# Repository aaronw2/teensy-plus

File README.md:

Teensy Plus
Revision 3.3

Copyright (C) 2019 by Aaron Williams

This board is designed to be mounted to a PJRC Teensy 4.0 and 3.2 board.
It brings out the I/Os of the Teensy and provides a 3V to 5V level shifter
and a WS2813mini NeoPixel in order to drive up to four channels of
NeoPixels.  The 5V channels should be compatible with the FastLED library
for the Teensy 4.0 (not 3.2).  In addition, this board provides a switchable
12V, 500ma output for driving a fan or other 12V accessories.  Note that
while the boost circuit is fairly efficient that it will draw around 2.75 times
as much current at 5V as the 12V output, so at 500ma it could potentially
draw around 1.4 amps.  If the 12V is not needed then it does not need to be
stuffed.

This board is designed to be mounted back-to-back with the Teensy 3.2 or
4.0 board. Note that the extra pins on the back will not be accessible
once this board is soldered in place.  It can be connected by soldering
board headers or using headers and sockets.

Not all of the pins are used and not all need to be hooked up.

On/OFF, Program and VBat are not hooked up.  Additionally J9 does not
need to be connected and can be used for an additional 5V pin.

IO0, IO1, IO2 and IO3 are passed to the level shifter and IO23 is
connected to the enable pin of the level shifter.  IO3 then goes to
the WS2813mini.

3.3V is obtained from the Teensy board which cannot supply a lot of
current.  Please do not exceed 100ma.

J8 brings provides 3.3V, ground and IO4 through IO15.  The pinout is:
J8:
1.  3.3V
2.  GND
3.  IO0
4.  IO1
5.  IO2
6.  IO3
7.  IO5
8.  IO4
9.  IO10
10. IO11
11. IO12
12. IO13
13. IO14
14. IO15

These pins are directly connected.

J10 brings out the other pins along with the 5V level shifted pins.  Note
that the level shifted pins pass through 22 ohm resistors to help reduce
noise and can optionally have capacitors connected in order to create a
low-pass filter.

Pins 2-5 pass through the level shifter, however, pin1 is an output only
that is connected to the output of the WS2813mini.

J10:
1.  GND
2.  IO8  (5V)
3.  IO9  (5V)
4.  IO6  (5V)
5.  DO   (5V, output of WS2813-mini)
6.  IO17 (3.3v, bi-directional)
7.  IO18 (3.3v, bi-directional)
8.  IO19 (3.3v, bi-directional)
9.  IO20 (3.3v, bi-directional)
10. IO21 (3.3v, bi-directional)
11. IO22 (3.3v, bi-directional)
12. 3.3V (output)
13. 5V (output)
14. Ground

J11 is used for power input and output.
1. Ground
2. +5V
3. Ground
4. +5V
5. Ground
6. +5V
7. Ground
8. +3.3V

J12 is also used for power.
1. +5V
2. Ground

J201 provides 12V at up to 500ma.
1. GND
2. +12
3. Switched ground (IO17 high enables ground), used for turning fans on/off

Power: This board can either provide 5V or receive 5V from the Teensy.
Note that it expects a battery to not be hooked up and for the input
to already be regulated to 5V.

3.3V comes from the Teensy.  Note that the Teensy can only supply a limited
amount of current at 3.3V.

Level shifter:
A SN74AHCT125N buffer is used to provide 5V I/O.  IO23 is connected
directly to the enable pin and must be pulled low in order to enable the
5V I/O. Pulling IO23 high will tri-state the bi-directional level shifter.

NOTE: Only use the Texas Instraments SN74AHCT125N!  Other manufacturers
do not support 3V input.

BOM:
C1, C2, C4, C8, C13     CAP CER 0.1UF 16V X7R 0603
C3, C65, C12            CAP CER 1UF 25V X7R 0603
C9, C10, C11, C14       CAP CER 10UF 10V X7R 0805
D1                      WS2813-MINI neopixel, available from LCSC
RN1                     47K Panasonic EXB-Q16P473J Resistor Netowrk 15
U1                      SN74AHCT125N (TI only!!!)

12V BOM:
C201                    CAP CER 22UF 16V X5R 0603
C202                    CAP CER 0.1UF 16V X7R 0603
C203                    CAP CER 0.022UF 50V X7R 0603
C204                    CAP CER 820PF 50V X7R 0603
C205                    CAP CER 0.047UF 50V X7R 0603
C206                    CAP CER 47UF 16V X5R 1210
D201                    SS24FL DIODE SCHOTTKY 40V 2A SOD123F
Q201                    BSS214NW MOSFET N-CH 20V 1.5A SOT323
R201                    RES SMD 18.7K OHM 1% 1/10W 0603
R202                    RES SMD 1.62K OHM 1% 1/10W 0603
R203                    RES SMD 86.6K OHM 1% 1/10W 0603
R204                    RES SMD 10K OHM 1% 1/10W 0603
R205                    RES SMD 100K OHM 1% 1/10W 0603
                        (can use 86.6K or higher resistor)

All components except the WS2813-mini can be sourced from Digikey.
Why did I use a WS2813-mini? I bought a reel of 1500 of them and the
footprint I have is a bit smaller than the WS2812-mini.

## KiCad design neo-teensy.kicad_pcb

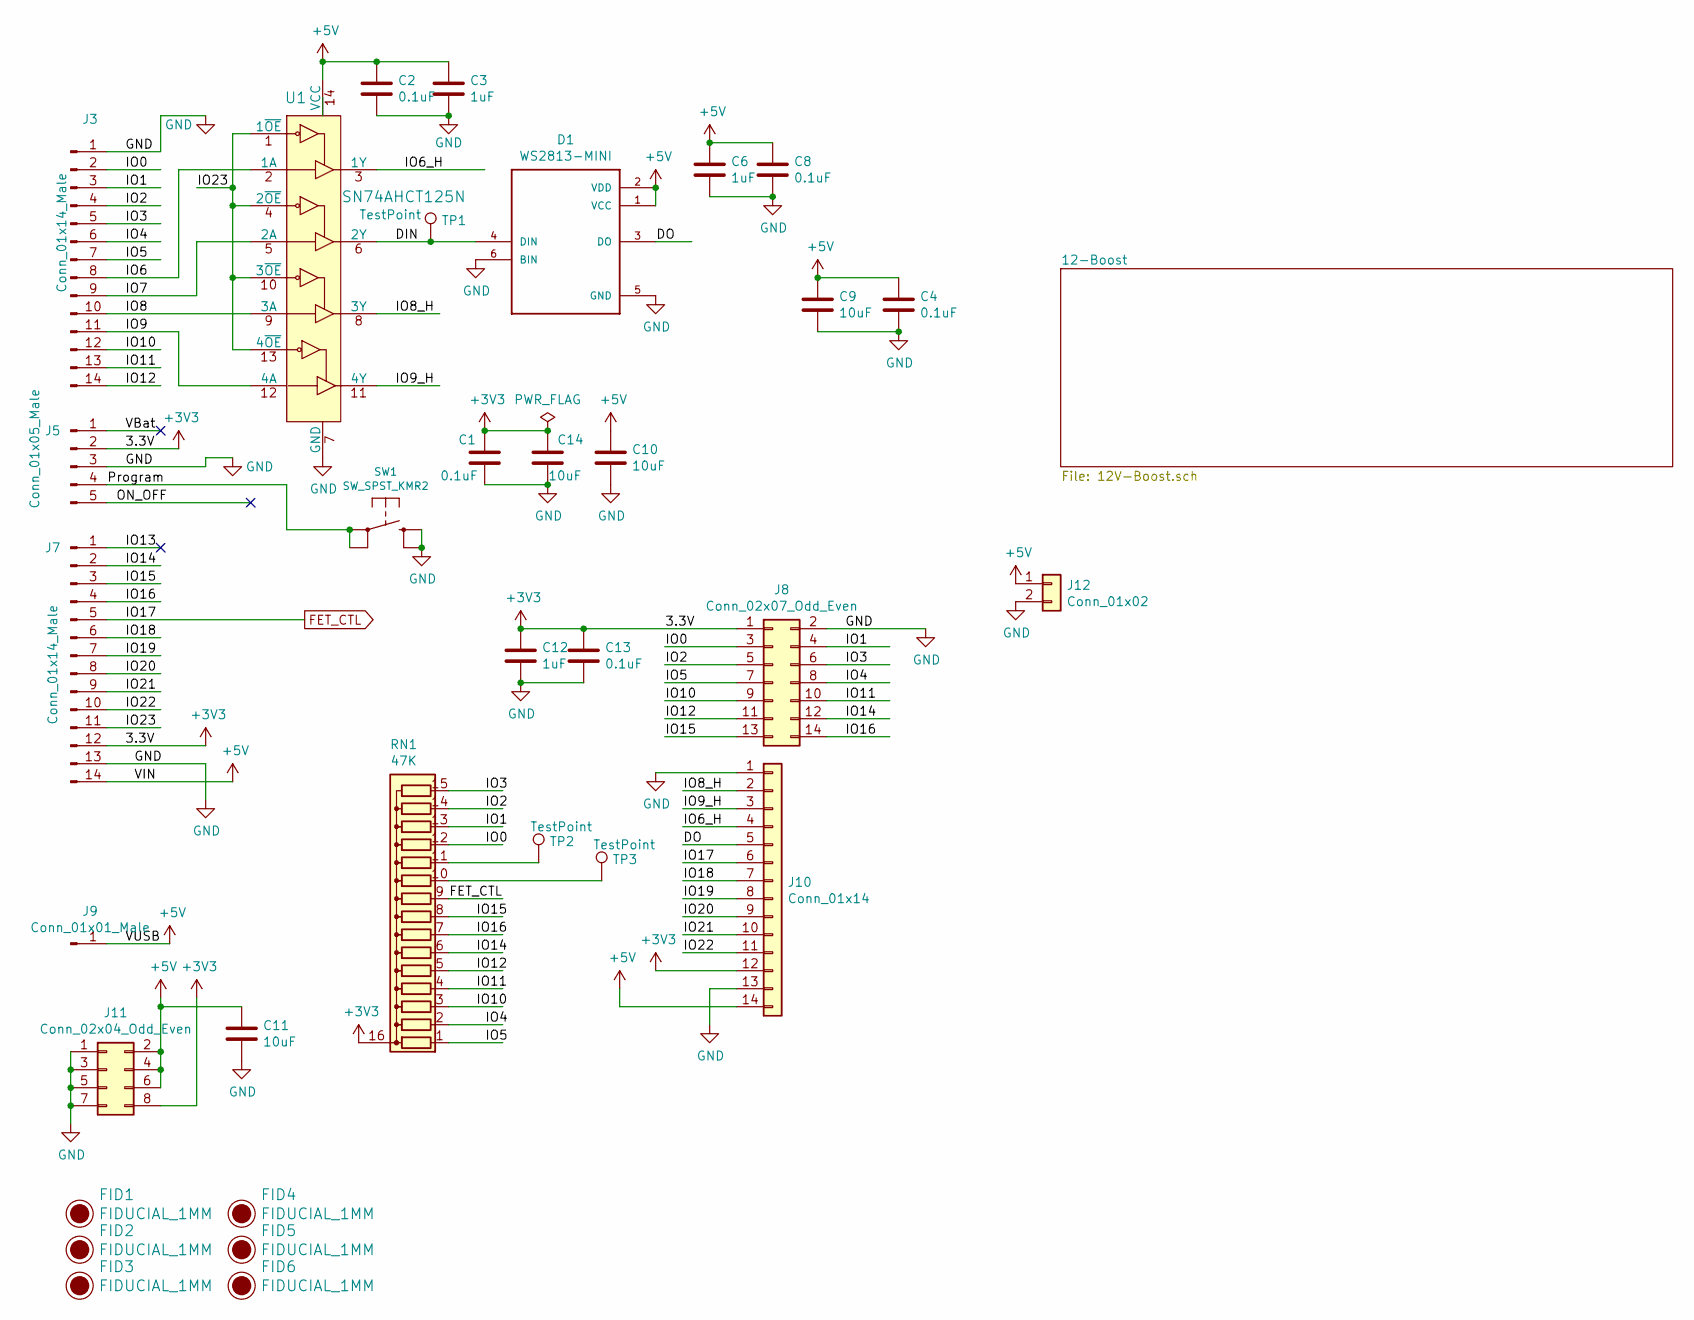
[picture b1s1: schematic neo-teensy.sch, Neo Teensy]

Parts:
C1, C2, C4, C8, C13: 0.1uF; C_0603_1608Metric; MPN CL10B104KO8WPNC
C3, C6, C12: 1uF; C_0603_1608Metric; MPN CL10B105KA8NNNC
C9, C10, C11, C14: 10uF; C_0805_2012Metric; MPN GRM21BR71A106KA73K
D1: WS2813-MINI; LED_WS2813-MINI-2; MPN WS2813-Mini(WS2813-3535)
FID1, FID2, FID3, FID4, FID5, FID6: FIDUCIAL_1MM; Fiducial_0.5mm_Mask1mm
J3, J7: Conn_01x14_Male; PinHeader_1x14_P2.54mm_Vertical
J5: Conn_01x05_Male; PinHeader_1x05_P2.54mm_Vertical
J8: Conn_02x07_Odd_Even; PinHeader_2x07_P2.54mm_Vertical
J9: Conn_01x01_Male; PinHeader_1x01_P2.54mm_Vertical
J10: Conn_01x14; PinHeader_1x14_P2.54mm_Vertical
J11: Conn_02x04_Odd_Even; PinHeader_2x04_P2.54mm_Vertical
J12: Conn_01x02; PinHeader_1x02_P2.54mm_Vertical
RN1: 47K; R_Array_Convex_8x0602; MPN EXB-Q16P473J
SW1: SW_SPST_KMR2; MPN KMR211NG LFS
TP1, TP2, TP3: TestPoint; TestPoint_Pad_D1.0mm
U1: SN74AHCT125N; Texas_S-PVQFN-N14; MPN SN74AHCT125RGYR; Digi-Key_PN 296-4655-5-ND

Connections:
+3V3: C1.1, C12.1, C13.1, C14.1, J5.2, J7.12, J8.1, J10.12, J11.8, RN1.16 (common)
+5V: C2.1, C3.1, C4.1, C6.1, C8.1, C9.1, C10.1, C11.1, D1.1 (VCC), D1.2 (VDD), J7.14, J9.1, J10.14, J11.2, J11.4, J11.6, J12.1, U1.14 (VCC); also elsewhere on the board
/DIN: D1.4 (DIN), TP1.1, U1.6 (2Y)
/DO: D1.3 (DO), J10.5
/IO0: J3.2, J8.3, RN1.12 (R11)
/IO1: J3.3, J8.4, RN1.13 (R12)
/IO2: J3.4, J8.5, RN1.14 (R13)
/IO3: J3.5, J8.6, RN1.15
/IO4: J3.6, J8.8, RN1.2 (R1)
/IO5: J3.7, J8.7, RN1.1
/IO6: J3.8, U1.2 (1A)
/IO6_H: J10.4, U1.3 (1Y)
/IO7: J3.9, U1.5 (2A)
/IO8: J3.10, U1.9 (3A)
/IO8_H: J10.2, U1.8 (3Y)
/IO9: J3.11, U1.12 (4A)
/IO9_H: J10.3, U1.11 (4Y)
/IO10: J3.12, J8.9, RN1.3 (R2)
/IO11: J3.13, J8.10, RN1.4 (R3)
/IO12: J3.14, J8.11, RN1.5 (R4)
/IO13: J7.1
/IO14: J7.2, J8.12, RN1.6 (R5)
/IO15: J7.3, J8.13, RN1.8 (R7)
/IO16: J7.4, J8.14, RN1.7 (R6)
/IO18: J7.6, J10.7
/IO19: J7.7, J10.8
/IO20: J7.8, J10.9
/IO21: J7.9, J10.10
/IO22: J7.10, J10.11
/IO23: J7.11, U1.1 (1~OE), U1.4 (2~OE), U1.10 (3~OE), U1.13 (4~OE)
/ON_OFF: J5.5
/Program: J5.4, SW1.1
/VBat: J5.1
FET_CTL: J7.5, J10.6, RN1.9 (R8); also elsewhere on the board
GND: C1.2, C2.2, C3.2, C4.2, C6.2, C8.2, C9.2, C10.2, C11.2, C12.2, C13.2, C14.2, D1.5 (GND), D1.6 (BIN), J3.1, J5.3, J7.13, J8.2, J10.1, J10.13, J11.1, J11.3, J11.5, J11.7, J12.2, SW1.2 (S), U1.7 (GND); also elsewhere on the board
unnamed: RN1.10 (R9), TP3.1
unnamed: RN1.11 (R10), TP2.1

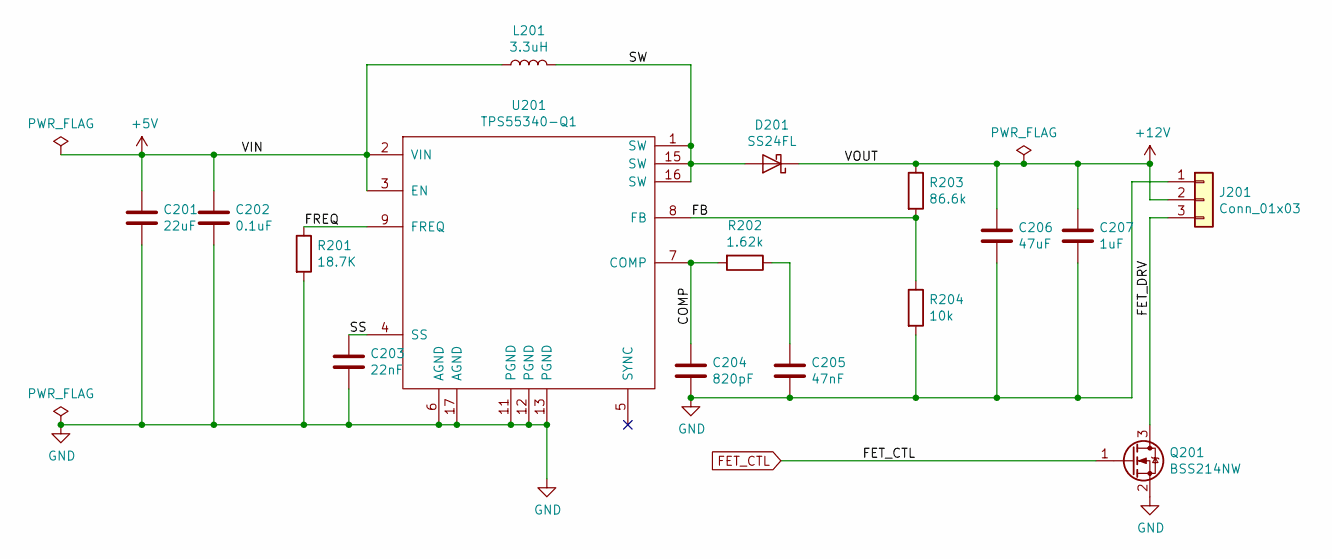
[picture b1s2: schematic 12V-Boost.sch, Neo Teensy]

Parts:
C201: 22uF; C_0603_1608Metric; MPN CL10A226MO7JZNC
C202: 0.1uF; C_0603_1608Metric; MPN CL10B104KO8WPNC
C203: 22nF; C_0603_1608Metric; MPN CL10B223KB8WPNC
C204: 820pF; C_0603_1608Metric; MPN C0603C821J5RACTU
C205: 47nF; C_0603_1608Metric; MPN CL10B473KB8WPNC
C206: 47uF; C_1210_3225Metric; MPN CL32A476KOJNNNE
C207: 1uF; C_0603_1608Metric; MPN CL10B105KA8NNNC
D201: SS24FL; D_SOD-123F; MPN SS24FL
J201: Conn_01x03; PinHeader_1x03_P2.54mm_Vertical
L201: 3.3uH; L_Vishay_IHLP-1212; MPN IHLP1212BZER3R3M11
Q201: BSS214NW; SOT-323_SC-70; MPN BSS214NWH6327XTSA1
R201: 18.7K; R_0603_1608Metric; MPN RC0603FR-0718K7L
R202: 1.62k; R_0603_1608Metric; MPN RC0603FR-071K62L
R203: 86.6k; R_0603_1608Metric; MPN CRCW060386K6FKEA
R204: 10k; R_0603_1608Metric; MPN CRCW060310K0FKEC
U201: TPS55340-Q1; QFN-16-1EP_3x3mm_P0.5mm_EP2.7x2.7mm_ThermalVias; MPN TPS55340RTER

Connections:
+5V: C201.1, C202.1, L201.1, U201.2 (VIN), U201.3 (EN); also elsewhere on the board
+12V: C206.1, C207.1, D201.1 (K), J201.2, R203.1
/12-Boost/COMP: C204.1, R202.2, U201.7 (COMP)
/12-Boost/FB: R203.2, R204.1, U201.8 (FB)
/12-Boost/FET_DRV: J201.3, Q201.3 (D)
/12-Boost/FREQ: R201.1, U201.9 (FREQ)
/12-Boost/SS: C203.1, U201.4 (SS)
/12-Boost/SW: D201.2 (A), L201.2, U201.1 (SW), U201.15 (SW), U201.16 (SW)
FET_CTL: Q201.1 (G); also elsewhere on the board
GND: C201.2, C202.2, C203.2, C204.2, C205.2, C206.2, C207.2, J201.1, Q201.2 (S), R201.2, R204.2, U201.6 (AGND), U201.11 (PGND), U201.12 (PGND), U201.13 (PGND), U201.17 (AGND); also elsewhere on the board
unnamed: C205.1, R202.1

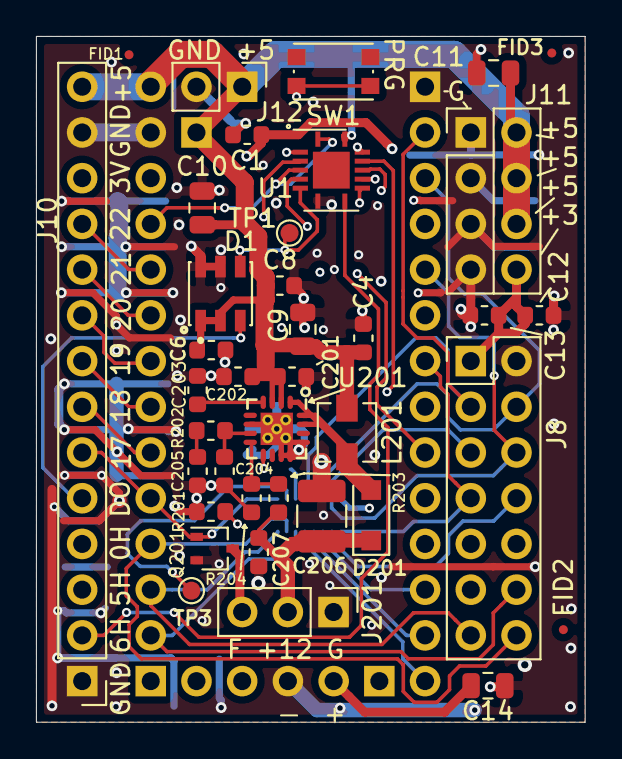
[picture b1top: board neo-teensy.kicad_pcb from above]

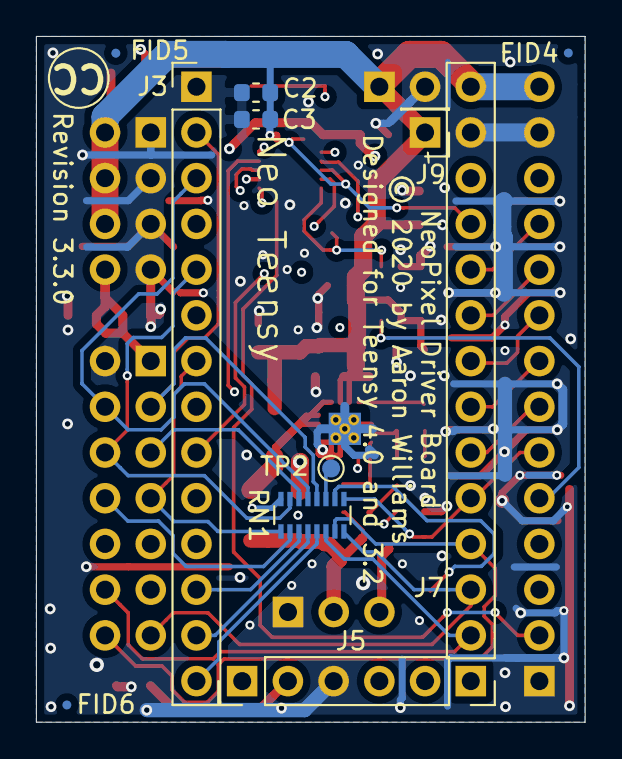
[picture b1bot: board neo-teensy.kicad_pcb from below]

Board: 4 copper layers, 30.5 x 38.1 mm, 49 parts (11 on the bottom side), 42 nets.

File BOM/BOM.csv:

Refs,Value,Footprint,Quantity,DESC,MFR,MPN,SPR,SPN,SPURL
L201,3.3uH,Aaron:L_Vishay_IHLP-1212,1,FIXED IND 3.3UH 2.7A 61 MOHM SMD,Vishay Dale,IHLP1212BZER3R3M11,Digikey,541-2567-1-ND,https://www.digikey.com/product-detail/en/IHLP1212BZER3R3M11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
U201,TPS55340-Q1,Aaron:QFN-16-1EP_3x3mm_P0.5mm_EP2.7x2.7mm_ThermalVias,1,IC REG BOOST ADJ 5.25A 16WQFN,TI,TPS55340RTER,Digikey,296-37677-1-ND,https://www.digikey.com/products/en?keywords=296-37677-1-ND
SW1,SW_SPST_KMR2,Aaron:SW_SPST_KMR2,1,SWITCH TACTILE SPST-NO 0.05A 32V,C&K,KMR211NG LFS,Digikey,CKN10243CT-ND,https://www.digikey.com/product-detail/en/c-k/KMR211NG-LFS/C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
C2;C13;C8;C4;C1;C202,0.1uF,Capacitor_SMD:C_0603_1608Metric,6,CAP CER 0.1UF 16V X7R 0603,Samsung,CL10B104KO8WPNC,Digikey,1276-6582-1-ND,https://www.digikey.com/products/en?keywords=1276-6582-1-ND
C3;C12;C6;C207,1uF,Capacitor_SMD:C_0603_1608Metric,4,CAP CER 1UF 25V X7R 0603,Samsung,CL10B105KA8NNNC,Digikey,1276-1184-1-ND,https://www.digikey.com/products/en?keywords=1276-1184-1-ND
C203,22nF,Capacitor_SMD:C_0603_1608Metric,1,CAP CER 0.022UF 50V X7R 0603,Samsung,CL10B223KB8WPNC,Digikey,1276-6534-1-ND,https://www.digikey.com/products/en?keywords=1276-6534-1-ND
C201,22uF,Capacitor_SMD:C_0603_1608Metric,1,CAP CER 22UF 16V X5R 0603,Samsung Electro-Mechanics,CL10A226MO7JZNC,Digikey,1276-7076-1-ND,https://www.digikey.com/products/en?keywords=1276-7076-1-ND
C205,47nF,Capacitor_SMD:C_0603_1608Metric,1,CAP CER 0.047UF 50V X7R 0603,Samsung Electro-Mechanics,CL10B473KB8WPNC,Digikey,1276-6540-1-ND,https://www.digikey.com/product-detail/en/samsung-electro-me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
C204,820pF,Capacitor_SMD:C_0603_1608Metric,1,CAP CER 820PF 50V X7R 0603,Kemet,C0603C821J5RACTU,Digikey,399-9127-1-ND,https://www.digikey.com/products/en?keywords=399-9127-1-ND
C14;C9;C11;C10,10uF,Capacitor_SMD:C_0805_2012Metric,4,CAP CER 10UF 10V X7R 0805,Murata Electronics,GRM21BR71A106KA73K,Digikey,490-14381-1-ND,https://www.digikey.com/products/en?keywords=490-14381-1-ND
C206,47uF,Capacitor_SMD:C_1210_3225Metric,1,CAP CER 47UF 16V X5R 1210,Samsung,CL32A476KOJNNNE,Digikey,1276-3376-1-ND,https://www.digikey.com/product-detail/en/samsung-electro-me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
J9,Conn_01x01_Male,Connector_PinHeader_2.54mm:PinHeader_1x01_P2.54mm_Vertical,1,-,-,-,-,-,-
J12,Conn_01x02,Connector_PinHeader_2.54mm:PinHeader_1x02_P2.54mm_Vertical,1,-,-,-,-,-,-
J201,Conn_01x03,Connector_PinHeader_2.54mm:PinHeader_1x03_P2.54mm_Vertical,1,-,-,-,-,-,-
J5,Conn_01x05_Male,Connector_PinHeader_2.54mm:PinHeader_1x05_P2.54mm_Vertical,1,-,-,-,-,-,-
J10,Conn_01x14,Connector_PinHeader_2.54mm:PinHeader_1x14_P2.54mm_Vertical,1,-,-,-,-,-,-
J3;J7,Conn_01x14_Male,Connector_PinHeader_2.54mm:PinHeader_1x14_P2.54mm_Vertical,2,-,-,-,-,-,-
J11,Conn_02x04_Odd_Even,Connector_PinHeader_2.54mm:PinHeader_2x04_P2.54mm_Vertical,1,-,-,-,-,-,-
J8,Conn_02x07_Odd_Even,Connector_PinHeader_2.54mm:PinHeader_2x07_P2.54mm_Vertical,1,-,-,-,-,-,-
D201,SS24FL,Diode_SMD:D_SOD-123F,1,DIODE SCHOTTKY 40V 2A SOD123F,ON,SS24FL,Digikey,SS24FLCT-ND,https://www.digikey.com/products/en?keywords=SS24FLCT-ND
D1,WS2813-MINI,LED_WS2813-mini:LED_WS2813-MINI-2,1,"RGB 620~625nm Red, 515~525nm Green, 465~475nm Blue SMD-6 Light Emitting Diodes (LED) RoHS",Worldsemi,WS2813-Mini(WS2813-3535),LCSC,C189639,https://lcsc.com/product-detail/Others_WS2813-Mini-WS2813-35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
U1,SN74AHCT125N,Package_DFN_QFN:Texas_S-PVQFN-N14,1,IC BUF NON-INVERT 5.5V 14VQFN,Texas Instruments,SN74AHCT125RGYR,Digikey,296-13910-1-ND,https://www.digikey.com/products/en?keywords=296-13910-1-ND
Q201,BSS214NW,Package_TO_SOT_SMD:SOT-323_SC-70,1,MOSFET N-CH 20V 1.5A SOT323,Infineon,BSS214NWH6327XTSA1,Digikey,BSS214NWH6327XTSA1CT-ND,https://www.digikey.com/products/en?keywords=BSS214NWH6327XT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
R202,1.62k,Resistor_SMD:R_0603_1608Metric,1,RES SMD 1.62K OHM 1% 1/10W 0603,Yageo,RC0603FR-071K62L,Digikey,311-1.62KHRCT-ND,https://www.digikey.com/product-detail/en/yageo/RC0603FR-071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
R204,10k,Resistor_SMD:R_0603_1608Metric,1,RES SMD 10K OHM 1% 1/10W 0603,Vishay Dale,CRCW060310K0FKEC,Digikey,541-2979-1-ND,https://www.digikey.com/products/en?keywords=541-2979-1-ND
R201,18.7K,Resistor_SMD:R_0603_1608Metric,1,RES SMD 18.7K OHM 1% 1/10W 0603,Yageo,RC0603FR-0718K7L,Digikey,311-18.7KHRCT-ND,https://www.digikey.com/product-detail/en/yageo/RC0603FR-071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
R203,86.6k,Resistor_SMD:R_0603_1608Metric,1,RES SMD 86.6K OHM 1% 1/10W 0603,Vishay Dale,CRCW060386K6FKEA,Digikey,541-86.6KHCT-ND,https://www.digikey.com/products/en?keywords=541-86.6KHCT-ND
RN1,47K,Resistor_SMD:R_Array_Convex_8x0602,1,RES ARRAY 15 RES 47K OHM 1506,Panasonic,EXB-Q16P473J,Digikey,U6473CT-ND,https://www.digikey.com/product-detail/en/panasonic-electron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

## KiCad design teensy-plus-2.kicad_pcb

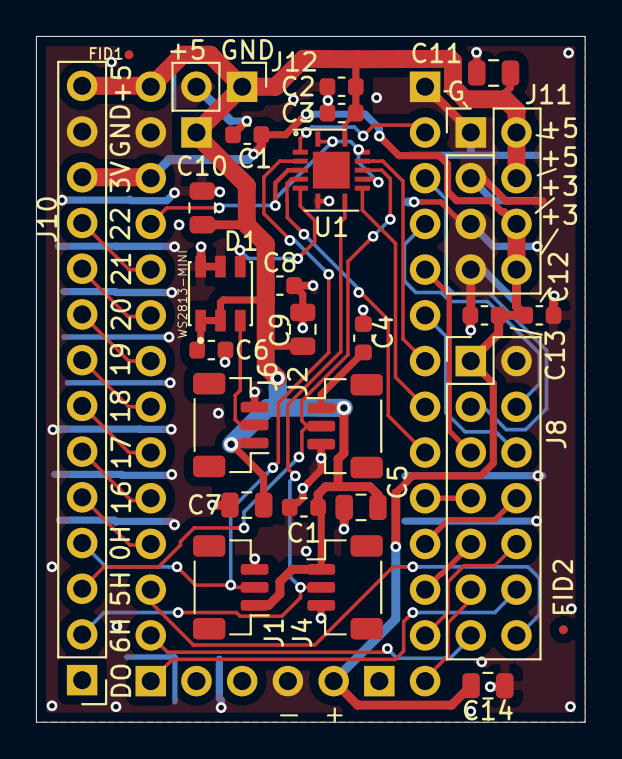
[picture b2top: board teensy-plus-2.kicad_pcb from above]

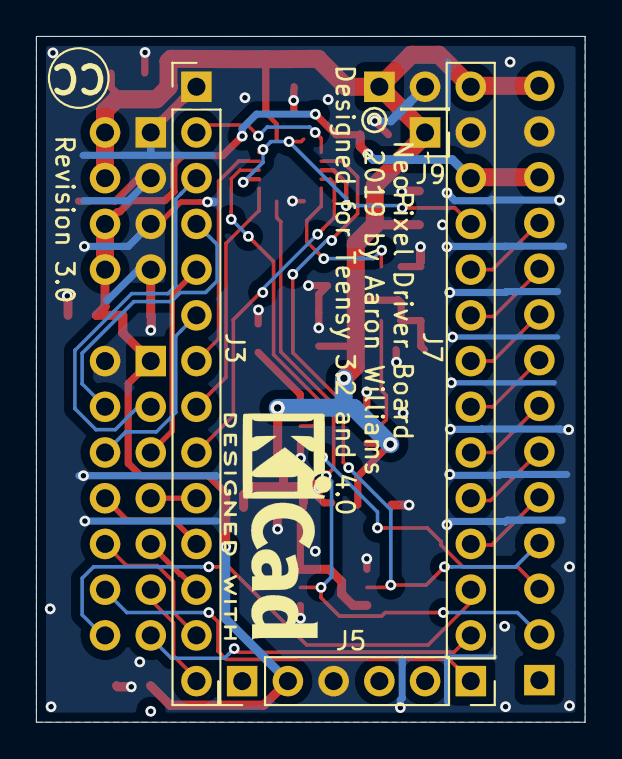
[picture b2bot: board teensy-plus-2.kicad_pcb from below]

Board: 2 copper layers, 30.5 x 38.1 mm, 31 parts (4 on the bottom side), 32 nets.

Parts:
C1, C1#2, C2, C4, C6, C8, C13: 0.1uF; C_0603_1608Metric
C3, C12: 1uF; C_0603_1608Metric
C5, C7, C9, C10, C11, C14: 10uF; C_0805_2012Metric
D1: WS2813-MINI; LED_WS2813-MINI-2
FID1, FID2: FIDUCIAL_1MM; Fiducial_0.5mm_Mask1mm
J1, J2, J4, J6: Conn_01x03_Male; JST_SH_BM03B-SRSS-TB_1x03-1MP_P1.00mm_Vertical
J3, J7: Conn_01x14_Male; PinHeader_1x14_P2.54mm_Vertical
J5: Conn_01x05_Male; PinHeader_1x05_P2.54mm_Vertical
J8: Conn_02x07_Odd_Even; PinHeader_2x07_P2.54mm_Vertical
J9: Conn_01x01_Male; PinHeader_1x01_P2.54mm_Vertical
J10: Conn_01x14; PinHeader_1x14_P2.54mm_Vertical
J11: Conn_02x04_Odd_Even; PinHeader_2x04_P2.54mm_Vertical
J12: Conn_01x02; PinHeader_1x02_P2.54mm_Vertical
U1: SN74AHCT125N; Texas_S-PVQFN-N14

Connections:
+3V3: C1#2.1, C12.1, C13.1, C14.1, J5.2, J7.12, J8.1, J10.12, J11.6, J11.8
+5V: C1.1, C2.1, C3.1, C4.1, C5.1, C6.1, C7.1, C8.1, C9.1, C10.1, C11.1, D1.1, D1.2, J1.1, J2.1, J4.1, J6.1, J7.14, J9.1, J10.14, J11.2, J11.4, J12.1, U1.14
/DIN: D1.4, U1.6
/DO: D1.3, J6.2
/IO0: J3.2, U1.2
/IO0_H: J1.2, J10.4, U1.3
/IO1: J3.3, J8.3
/IO2: J3.4, J8.4
/IO3: J3.5, J8.5
/IO4: J3.6, J8.6
/IO5: J3.7, U1.12
/IO5_H: J2.2, J10.3, U1.11
/IO6: J3.8, U1.9
/IO6_H: J4.2, J10.2, U1.8
/IO7: J3.9, U1.5
/IO8: J3.10, J8.7
/IO9: J3.11, J8.8
/IO10: J3.12, J8.9
/IO11: J3.13, J8.10
/IO12: J3.14, J8.11
/IO13: J7.1, J8.12
/IO14: J7.2, J8.13
/IO15: J7.3, J8.14
/IO16: J7.4, J10.5
/IO17: J7.5, J10.6
/IO18: J7.6, J10.7
/IO19: J7.7, J10.8
/IO20: J7.8, J10.9
/IO21: J7.9, J10.10
/IO22: J7.10, J10.11
/IO23: J7.11, U1.1, U1.4, U1.10, U1.13
GND: C1.2, C1#2.2, C2.2, C3.2, C4.2, C5.2, C6.2, C7.2, C8.2, C9.2, C10.2, C11.2, C12.2, C13.2, C14.2, D1.5, D1.6, J1.3, J2.3, J3.1, J4.3, J5.3, J6.3, J7.13, J8.2, J10.13, J11.1, J11.3, J11.5, J11.7, J12.2, U1.7

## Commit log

2019-11-11 Initial commit of revision 1.1.
2019-11-17 Changed 5V I/O pins to be compatible with FastLED
    Also updated the README and other minor cleanups.
2019-11-17 Changed 5V I/O pins to be compatible with FastLED
    Also updated the README and added a BOM and other minor cleanups.
2019-11-20 Committed version 2.0
    - Board is smaller
    - Now designed to be mounted to the bottom of a Teensy
    - Added connector to solder on 12V supply.
2019-11-21 Updated to version 3.0
    - Changed to 74AHCT125
    - Removed 22 ohm resistors
    - IO23 is now active low
2019-11-21 Minor silk screen change. Retag 3.0.0
2019-11-21 Renamed project neo-teensy
    Rev 3.0
2019-11-21 Minor silk-screen fix.
2019-11-21 Minor cleanup.
2019-11-22 Updated BOM
2019-11-25 Removed connectors and added 12V boost
    Version 3.1.0
2019-12-01 Fixed GPIO 13, GPIO 16 and GPIO 17 for the fan control.
2019-12-01 Minor fixups, changed solder mask.
2019-12-30 Changed GPIOs for Teensy 4.0
    The 5V GPIOs were changed for the Teensy 4.0. In addition the GPIOs to
    the 14 pin header were also changed.
    Some component values were also changed for the power supply.
    Note that this is still compatible with the 3.1 stencil.
    This also fixes the 12V BOM.
2020-01-01 Added pull-up resistors to 14-pin header
    Made board 4 layers
    Made board double sided

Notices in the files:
12V-Boost.sch:
Copyright (C) 2019 Aaron Williams
neo-teensy.kicad_pcb:
© 2020 by Aaron Williams
teensy-plus-2.kicad_pcb:
© 2019 by Aaron Williams
